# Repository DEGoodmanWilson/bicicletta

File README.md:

BICICLETTA
==========

Bicicletta is an open source iOS / Android interface for your electric bicycle.

You can read more about this project on the project's [Github Page](http://degoodmanwilson.github.io/bicicletta/)

FIRMWARE LICENSE
================

Copyright © D.E. Goodman-Wilson 2014.

Bicicletta Firmware is free software: you can redistribute it and/or modify
it under the terms of the GNU General Public License as published by
the Free Software Foundation, either version 3 of the License, or
(at your option) any later version.

This program is distributed in the hope that it will be useful,
but WITHOUT ANY WARRANTY; without even the implied warranty of
MERCHANTABILITY or FITNESS FOR A PARTICULAR PURPOSE.  See the
GNU General Public License for more details.

You should have received a copy of the GNU General Public License
along with Bicicletta Firmware.  If not, see <http://www.gnu.org/licenses/>.

The full text of the license is available in /firmware/LICENSE.txt

HARDWARE LICENSE
================

Copyright © D.E. Goodman-Wilson 2014.

This documentation describes Open Hardware and is licensed under the
CERN OHL v. 1.2.

You may redistribute and modify this documentation under the terms of the
CERN OHL v.1.2. (http://ohwr.org/cernohl). This documentation is distributed
WITHOUT ANY EXPRESS OR IMPLIED WARRANTY, INCLUDING OF
MERCHANTABILITY, SATISFACTORY QUALITY AND FITNESS FOR A
PARTICULAR PURPOSE. Please see the CERN OHL v.1.2 for applicable
conditions.

The full text of the license is available in /hardware/LICENSE.txt

You can read more about how the CERN OHL license applies to this project [on the CERN website](http://www.ohwr.org/attachments/2392/cern_ohl_v_1_2_howto.pdf).

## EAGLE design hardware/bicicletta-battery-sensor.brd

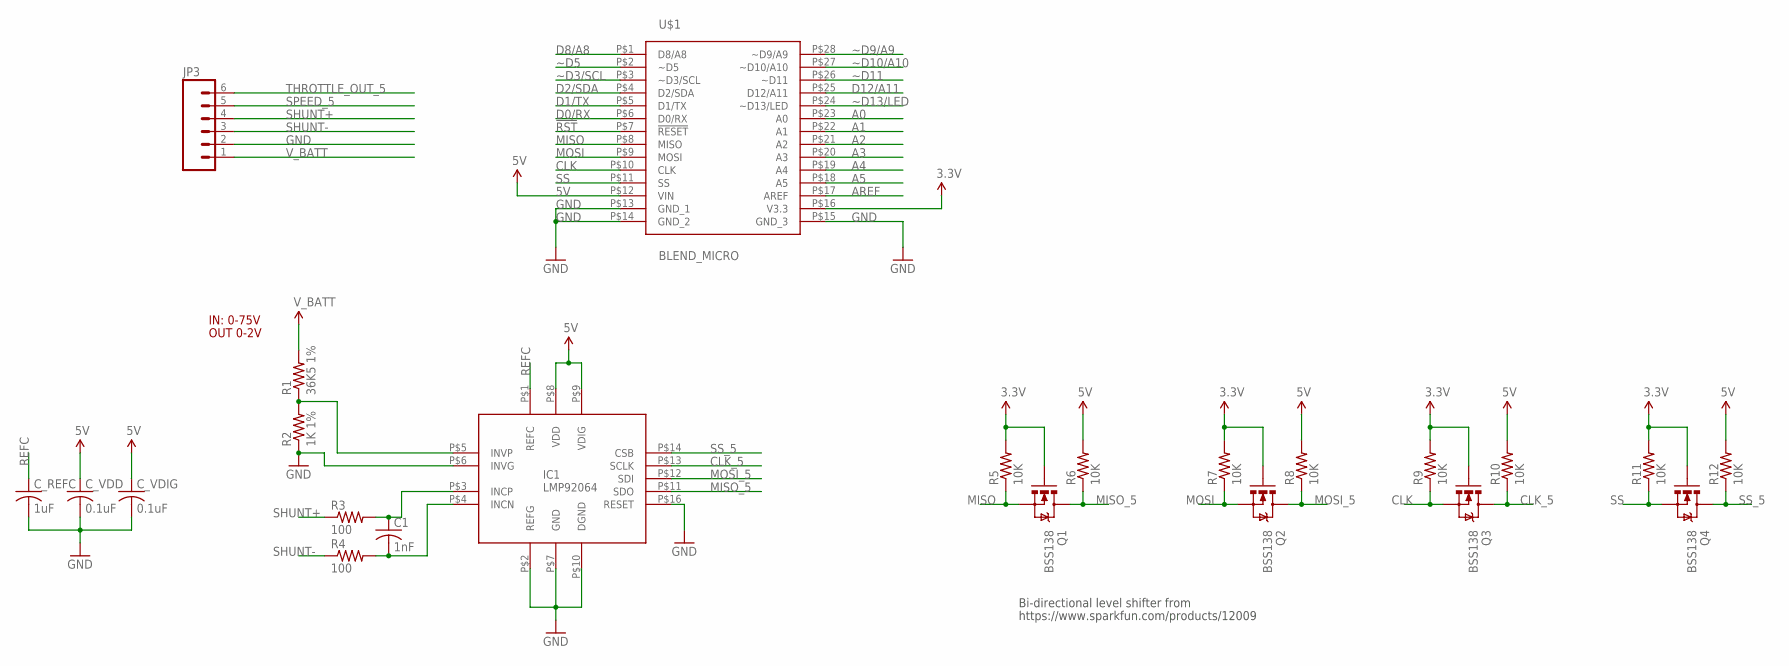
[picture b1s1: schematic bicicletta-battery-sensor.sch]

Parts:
C1: 1nF; C0603
C_REFC: 1uF; C0603
C_VDD: 0.1uF; C0603
C_VDIG: 0.1uF; C0603
IC1: LMP92064; WSON-16
JP3: M06SIP; 1X06
Q1, Q2, Q3, Q4: BSS138; SOT23-3
R1: 36K5 1%; R0603
R2: 1K 1%; R0603
R3, R4: 100; R0603
R5, R6, R7, R8, R9, R10, R11, R12: 10K; R0603
U$1: BLEND_MICRO

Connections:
3.3V: Q1.1 (G), Q2.1 (G), Q3.1 (G), Q4.1 (G), R5.2, R7.2, R9.2, R11.2, U$1.P$16 (V3.3)
5V: C_VDD.1, C_VDIG.1, IC1.P$8 (VDD), IC1.P$9 (VDIG), R6.2, R8.2, R10.2, R12.2, U$1.P$12 (VIN)
!RST: U$1.P$7 (!RESET)
A0: U$1.P$23 (A0)
A1: U$1.P$22 (A1)
A2: U$1.P$21 (A2)
A3: U$1.P$20 (A3)
A4: U$1.P$19 (A4)
A5: U$1.P$18 (A5)
AREF: U$1.P$17 (AREF)
CLK: Q3.2 (S), R9.1, U$1.P$10 (CLK)
CLK_5: IC1.P$13 (SCLK), Q3.3 (D), R10.1
D0/RX: U$1.P$6 (D0/RX)
D1/TX: U$1.P$5 (D1/TX)
D2/SDA: U$1.P$4 (D2/SDA)
D8/A8: U$1.P$1 (D8/A8)
D12/A11: U$1.P$25 (D12/A11)
GND: C_REFC.2, C_VDD.2, C_VDIG.2, IC1.P$2 (REFG), IC1.P$6 (INVG), IC1.P$7 (GND), IC1.P$10 (DGND), IC1.P$16 (RESET), JP3.2, R2.1, U$1.P$13 (GND_1), U$1.P$14 (GND_2), U$1.P$15 (GND_3)
MISO: Q1.2 (S), R5.1, U$1.P$8 (MISO)
MISO_5: IC1.P$11 (SDO), Q1.3 (D), R6.1
MOSI: Q2.2 (S), R7.1, U$1.P$9 (MOSI)
MOSI_5: IC1.P$12 (SDI), Q2.3 (D), R8.1
unnamed: IC1.P$5 (INVP), R1.1, R2.2
unnamed: C1.1, IC1.P$3 (INCP), R3.2
unnamed: C1.2, IC1.P$4 (INCN), R4.2
REFC: C_REFC.1, IC1.P$1 (REFC)
SHUNT+: JP3.4, R3.1
SHUNT-: JP3.3, R4.1
SPEED_5: JP3.5
SS: Q4.2 (S), R11.1, U$1.P$11 (SS)
SS_5: IC1.P$14 (CSB), Q4.3 (D), R12.1
THROTTLE_OUT_5: JP3.6
V_BATT: JP3.1, R1.2
~D3/SCL: U$1.P$3 (~D3/SCL)
~D5: U$1.P$2 (~D5)
~D9/A9: U$1.P$28 (~D9/A9)
~D10/A10: U$1.P$27 (~D10/A10)
~D11: U$1.P$26 (~D11)
~D13/LED: U$1.P$24 (~D13/LED)

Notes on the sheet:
IN: 0-75V
OUT 0-2V
Bi-directional level shifter from
https://www.sparkfun.com/products/12009

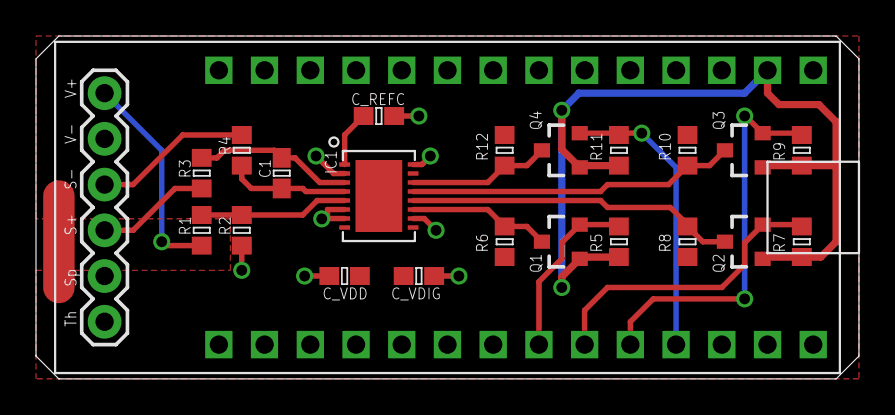
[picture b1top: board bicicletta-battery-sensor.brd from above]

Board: 2 copper layers, 45.7 x 19.1 mm, 24 parts (1 on the bottom side), 18 nets.

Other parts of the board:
U$2: RAILSTARS_25MM

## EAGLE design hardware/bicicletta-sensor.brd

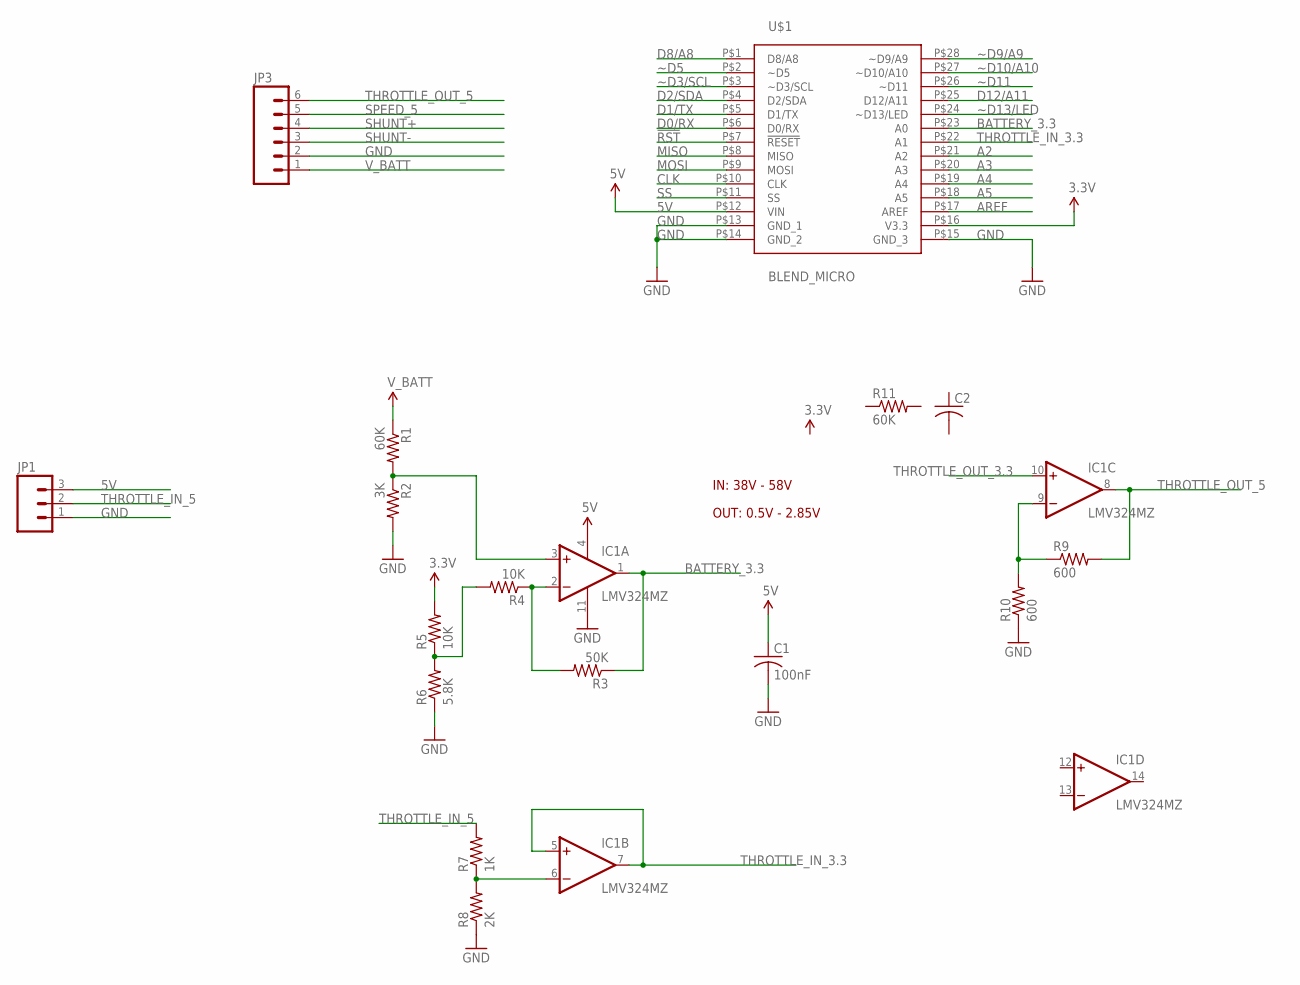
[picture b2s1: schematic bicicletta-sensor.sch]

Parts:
C1: 100nF; C0603
C2: C-USC0603; C0603
IC1: LMV324MZ; TSSOP14
JP1: M03PTH; 1X03
JP3: M06SIP; 1X06
R1, R11: 60K; R0603
R2: 3K; R0603
R3: 50K; R0603
R4, R5: 10K; R0603
R6: 5.8K; R0603
R7: 1K; R0603
R8: 2K; R0603
R9, R10: 600; R0603
U$1: BLEND_MICRO

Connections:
3.3V: R5.2, U$1.P$16 (V3.3)
5V: C1.1, IC1.4 (V+), JP1.3, U$1.P$12 (VIN)
!RST: U$1.P$7 (!RESET)
A2: U$1.P$21 (A2)
A3: U$1.P$20 (A3)
A4: U$1.P$19 (A4)
A5: U$1.P$18 (A5)
AREF: U$1.P$17 (AREF)
BATTERY_3.3: IC1.1 (OUT), R3.1, U$1.P$23 (A0)
BIAS: R4.2, R5.1, R6.2
CLK: U$1.P$10 (CLK)
D0/RX: U$1.P$6 (D0/RX)
D1/TX: U$1.P$5 (D1/TX)
D2/SDA: U$1.P$4 (D2/SDA)
D8/A8: U$1.P$1 (D8/A8)
D12/A11: U$1.P$25 (D12/A11)
GND: C1.2, IC1.11 (V-), JP1.1, JP3.2, R2.2, R6.1, R8.1, R10.1, U$1.P$13 (GND_1), U$1.P$14 (GND_2), U$1.P$15 (GND_3)
MISO: U$1.P$8 (MISO)
MOSI: U$1.P$9 (MOSI)
unnamed: IC1.9 (-IN), R9.1, R10.2
unnamed: IC1.3 (+IN), R1.2, R2.1
unnamed: IC1.2 (-IN), R3.2, R4.1
unnamed: IC1.6 (-IN), R7.1, R8.2
SHUNT+: JP3.4
SHUNT-: JP3.3
SPEED_5: JP3.5
SS: U$1.P$11 (SS)
THROTTLE_IN_3.3: IC1.5 (+IN), IC1.7 (OUT), U$1.P$22 (A1)
THROTTLE_IN_5: JP1.2, R7.2
THROTTLE_OUT_3.3: IC1.10 (+IN)
THROTTLE_OUT_5: IC1.8 (OUT), JP3.6, R9.2
V_BATT: JP3.1, R1.1
~D3/SCL: U$1.P$3 (~D3/SCL)
~D5: U$1.P$2 (~D5)
~D9/A9: U$1.P$28 (~D9/A9)
~D10/A10: U$1.P$27 (~D10/A10)
~D11: U$1.P$26 (~D11)
~D13/LED: U$1.P$24 (~D13/LED)

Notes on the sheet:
IN: 38V - 58V
OUT: 0.5V - 2.85V

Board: 2 copper layers, 18 parts (1 on the bottom side), 13 nets, no tracks yet.

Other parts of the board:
U$2: RAILSTARS_25MM

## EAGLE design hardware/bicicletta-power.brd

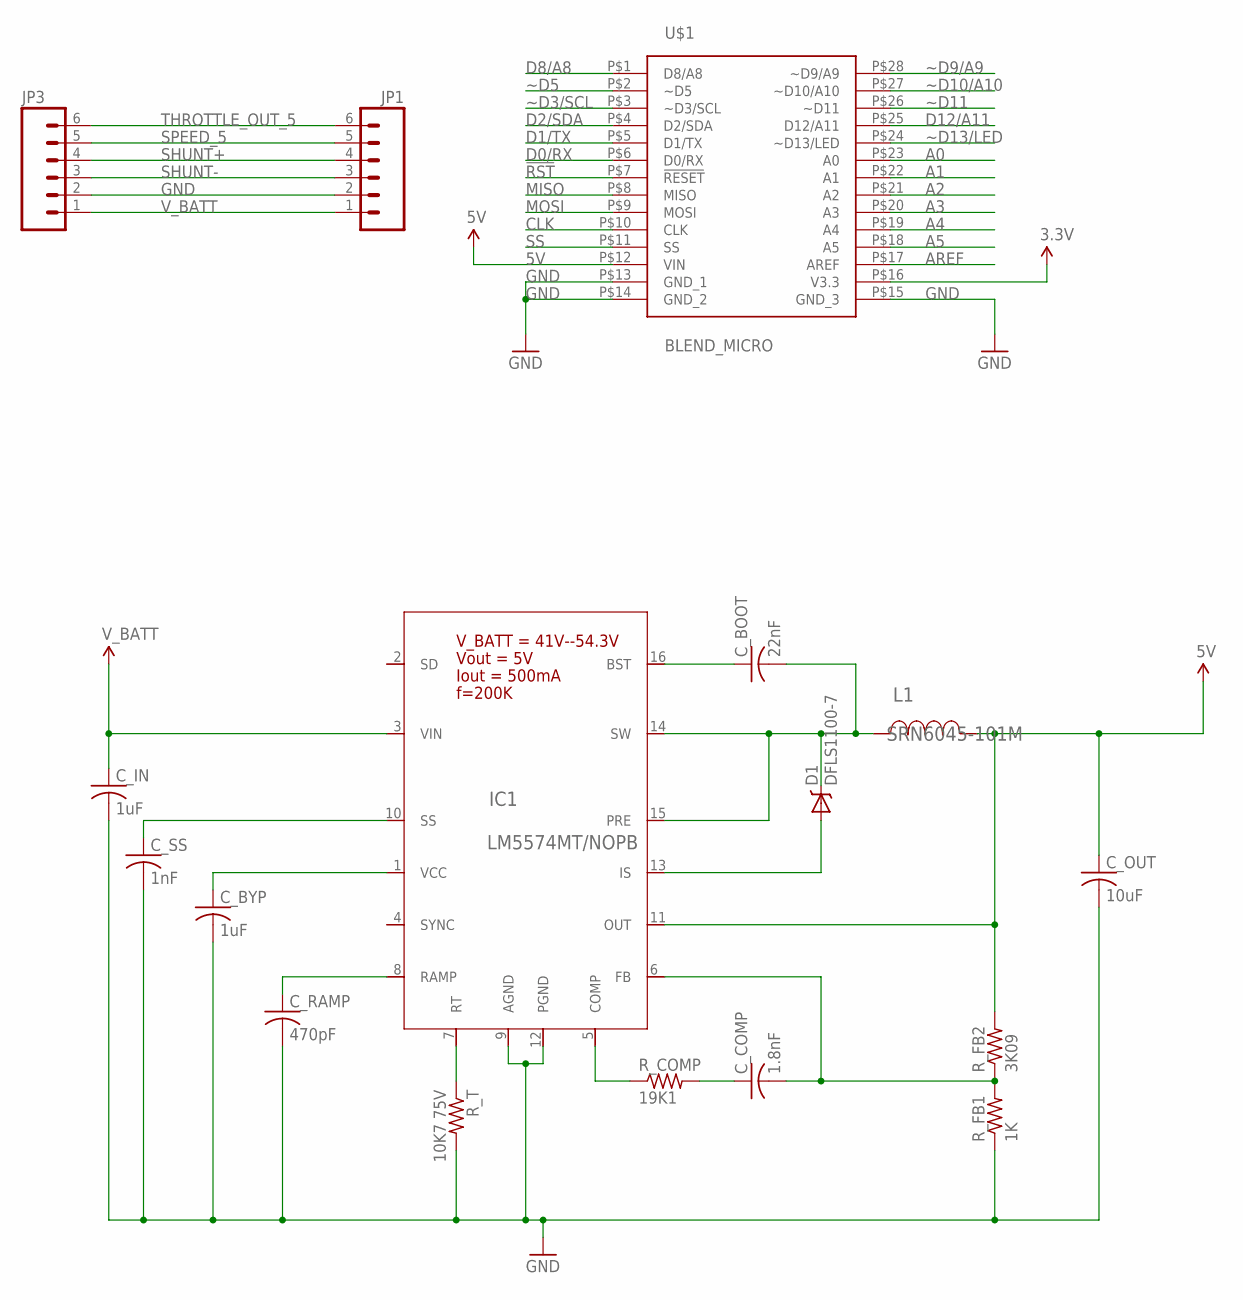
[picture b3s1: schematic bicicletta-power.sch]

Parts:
C_BOOT: 22nF; C0603
C_BYP: 1uF; C0603
C_COMP: 1.8nF; C0603
C_IN: 1uF; C1206
C_OUT: 10uF; C0805
C_RAMP: 470pF; C0603
C_SS: 1nF; C0603
D1: DFLS1100-7; POWERDI123
IC1: LM5574MT/NOPB; MTC16
JP1, JP3: M06SIP; 1X06
L1: SRN6045-101M; SRN6045
R_COMP: 19K1; R0603
R_FB1: 1K; R0603
R_FB2: 3K09; R0603
R_T: 10K7 75V; R0603
U$1: BLEND_MICRO

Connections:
3.3V: U$1.P$16 (V3.3)
5V: C_OUT.1, IC1.11 (OUT), L1.2, R_FB2.2, U$1.P$12 (VIN)
!RST: U$1.P$7 (!RESET)
A0: U$1.P$23 (A0)
A1: U$1.P$22 (A1)
A2: U$1.P$21 (A2)
A3: U$1.P$20 (A3)
A4: U$1.P$19 (A4)
A5: U$1.P$18 (A5)
AREF: U$1.P$17 (AREF)
CLK: U$1.P$10 (CLK)
D0/RX: U$1.P$6 (D0/RX)
D1/TX: U$1.P$5 (D1/TX)
D2/SDA: U$1.P$4 (D2/SDA)
D8/A8: U$1.P$1 (D8/A8)
D12/A11: U$1.P$25 (D12/A11)
GND: C_BYP.2, C_IN.2, C_OUT.2, C_RAMP.2, C_SS.2, IC1.9 (AGND), IC1.12 (PGND), JP1.2, JP3.2, R_FB1.1, R_T.2, U$1.P$13 (GND_1), U$1.P$14 (GND_2), U$1.P$15 (GND_3)
MISO: U$1.P$8 (MISO)
MOSI: U$1.P$9 (MOSI)
unnamed: C_SS.1, IC1.10 (SS)
unnamed: C_BYP.1, IC1.1 (VCC)
unnamed: C_RAMP.1, IC1.8 (RAMP)
unnamed: IC1.7 (RT), R_T.1
unnamed: C_COMP.2, IC1.6 (FB), R_FB1.2, R_FB2.1
unnamed: C_COMP.1, R_COMP.2
unnamed: IC1.5 (COMP), R_COMP.1
unnamed: D1.A, IC1.13 (IS)
unnamed: C_BOOT.1, IC1.16 (BST)
unnamed: C_BOOT.2, D1.K, IC1.14 (SW), IC1.15 (PRE), L1.1
SHUNT+: JP1.4, JP3.4
SHUNT-: JP1.3, JP3.3
SPEED_5: JP1.5, JP3.5
SS: U$1.P$11 (SS)
THROTTLE_OUT_5: JP1.6, JP3.6
V_BATT: C_IN.1, IC1.3 (VIN), JP1.1, JP3.1
~D3/SCL: U$1.P$3 (~D3/SCL)
~D5: U$1.P$2 (~D5)
~D9/A9: U$1.P$28 (~D9/A9)
~D10/A10: U$1.P$27 (~D10/A10)
~D11: U$1.P$26 (~D11)
~D13/LED: U$1.P$24 (~D13/LED)

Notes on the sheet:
f=200K
V_BATT = 41V--54.3V
Vout = 5V
Iout = 500mA

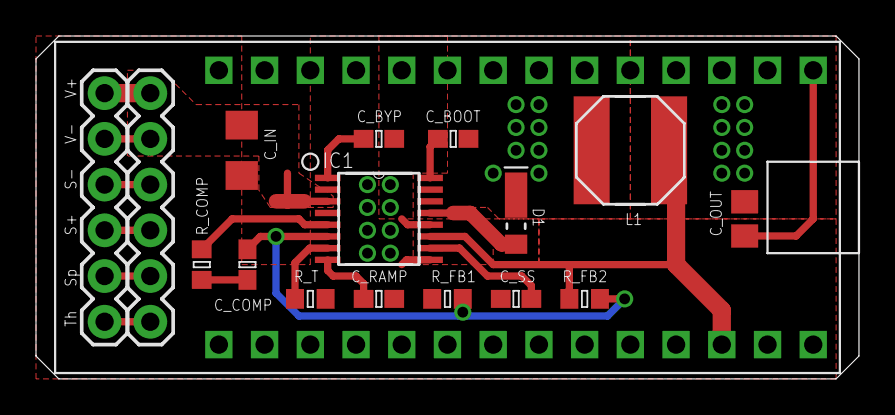
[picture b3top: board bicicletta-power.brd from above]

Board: 2 copper layers, 45.7 x 19.1 mm, 18 parts (1 on the bottom side), 17 nets.

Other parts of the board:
U$2: RAILSTARS_25MM

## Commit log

2014-08-10 BLEduino in schematic.
2014-08-28 Switching regulator is set up in schematic.
2014-09-02 Added 3.3V LDO regulator
2014-09-02 Added analog voltage shifter of dubious quality. WOrks in simulation
2014-09-02 Here is the circuit.jar design for the analog level-shifter.
2014-09-02 Oh wait, this isn't for the throttle, this is for level-shifting the battery input. The input is scaled from 38-58V to 0-3.3V. Roughly.
2014-09-02 Fixed battery voltage shifter, added level shifter for throttle (5V hall effect sensor)
2014-09-03 Refactored the ripple feedback circuit on the switching regulator
2014-09-04 Beginning to refactor design into stackable modules.
2014-09-04 Adding connectors.
2014-09-04 Error in regulator connections. Please double check
2014-09-04 Adding PCB layout.
2014-09-05 Close to final layout on switching regulator.
2014-09-05 Fine tuning
2014-09-05 nudging
2014-09-05 Updated to include actual component for the BLEND MICRO
2014-09-06 Wider voltage range on the op-amp level shifter, refinements on the PCB layout
2014-09-08 Rethinking the PCB layout to be more compact.
2014-09-08 More compact still. Need to check solderability.
2014-09-09 Layout of switching regulator is nearing finalization.
2014-09-09 First final draft of PCB layout. Requires validation.
2014-09-09 Inductor speced out. PCB placement getting closer.
2014-09-19 SMall tweaks that add up.
2014-09-19 HULK SMASH!
2014-09-19 labels cleaned up
2014-09-20 Futzing with the ground planes and via tenting.
2014-09-29 To hell with the buck regulator, let's just take 5V from the controller.
2014-09-30 Revert "To hell with the buck regulator, let's just take 5V from the controller."
    This reverts commit f16ee5c0247fff79c0027ea9109af273bc1d2e81.
2014-10-08 Why not use the Blend's 150mA 3.3V regulator?
2014-11-12 There it is. Order that.
2014-11-13 Finalizations.
2014-11-17 Final silkscreen
2014-11-17 Empty sensor boards.
2014-11-20 Better analog design. Still working on DAC for throttle output.
2014-11-29 Unsure what all has changed…
2014-11-29 More README. Licensing information.
2014-11-29 Firmware license.
2014-11-29 Removal of whitespace
2014-11-29 Whitespace.
2014-11-29 Create gh-pages branch via GitHub
2014-11-29 Revert "Create gh-pages branch via GitHub"
    This reverts commit a3c387f312e58dbb962f2532eb12fe27564131d6.
2014-11-29 New website with Jekyll
2014-11-29 Layout that works for me.
2014-11-30 A Gemfile. Because.
2014-11-30 Some corrections.
2014-11-30 Now we have some content.
2014-11-30 More details.
2014-12-01 new 8-bit pics for frontpage
2014-12-03 Let's use the LMP92064!
2014-12-03 Add level shifter
2014-12-03 preliminary routing of voltage and current sense PCB
2014-12-03 Nearly finalized PCB for battery sensor module
2014-12-03 Some start on the battery sensor module page
2014-12-03 Add value to the TXB0108
2014-12-03 Details on design of battery sensor.
2014-12-03 More notes.
2014-12-04 Detailed notes on the power module design.
2014-12-04 Include module status
2014-12-04 More status updates
2014-12-04 Typos
2014-12-04 A little more space on the resistors for ease of soldering
2014-12-04 Yeah
2014-12-04 Update timestamp on sensor PCB
2014-12-05 First firmware commit. Very barebones.
2014-12-05 Compiles. Needs a small change to the BLE library for some reason.
    Add
    include "lib_aci.h" to aci_setup.h
2014-12-05 include cleanup
2014-12-11 More skeleton code.
2014-12-11 And again. Forgot to add this file.
2015-09-13 Trying out a new level shifter, as the previous integrated one proved awfully fiddly in practice.
2015-09-13 I don't know when these changes were made, or what they do.
2015-09-13 Tidying some traces up.

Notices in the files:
parts and their libraries:
SparkFun-Connectors: Licensing: CC v3.0 Share-Alike You are welcome to use this library for commercial purposes.
SparkFun-DiscreteSemi: Licensing: Creative Commons ShareAlike 4.0 International - https://creativecommons.org/licenses/by-sa/4.0
